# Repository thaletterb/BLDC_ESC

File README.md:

## MSP430 Brushless DC Motor Electronic Speed Controller 

Development of an MSP430 based electronic speed controller. 
* Controls a BLDC electric motor for speed/torque
* Trapezoidal control scheme (6 Step Commutation)

## Background 

* Electronic Speed Control (ESC) is an electronic circuit that controls and regulates the speed of an electric motor. 
* SIMONK ESCs are commonly used for applications such as quadcopters or RC cars
* The purpose of this project is to develop an MSP430 based ESC which replicates the functionality of an off the shelf controller

## Hardware Architecture 

* Current implementation:
  * HW Revision 2
  * 

* Revision History
  * Revision 2 
    * 1 MSP430F5529 PCBA 
    * 1 LHI 2212 920KV Brushless Motor
    * 6 IRLR120N MOSFET N Channel 
    * 3 IR2104S IC Gate Driver 
  * Revision 1 
    * 1 MSP430F5529 Launchpad
    * 1 LHI 2212 920KV Brushless Motor
    * 1 SIMONK 30A ESC
    * 1 Potentiometer to act as throttle input

## Software Architecture

* TI-RTOS
* Current phase of implementation consists of:
  * Using MSP430 to generate varying width PWM signals to the SIMONK ESC
  * Potentiometer attached to analog input P6.1
* Periodics
  * 50Hz CLK

## Software Requirements

Software is based on MSP430F5529 launchpad, running TI-RTOS.

* Code Composer Studio (ver 8.3.1)
  * http://www.ti.com/tool/CCSTUDIO
* TI-RTOS MSP43x 2.20.00.06 
  * http://software-dl.ti.com/dsps/dsps_public_sw/sdo_sb/targetcontent/tirtos/index.html

## References
* https://en.wikipedia.org/wiki/Electronic_speed_control 
* https://www.instructables.com/id/Make-Your-Own-ESC/ 
* http://www.ti.com/lit/ug/spruhu4e/spruhu4e.pdf
* https://simple-circuit.com/arduino-sensorless-bldc-motor-controller-esc/

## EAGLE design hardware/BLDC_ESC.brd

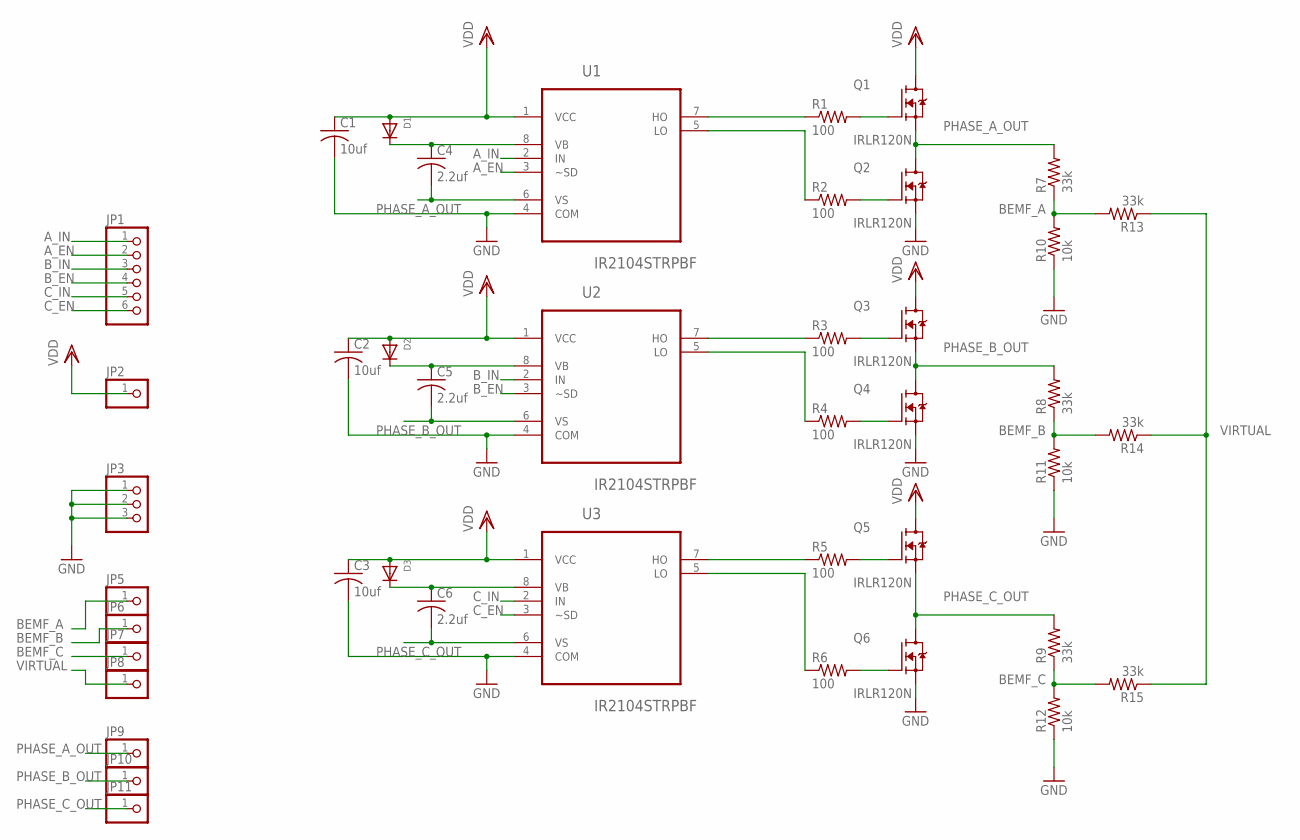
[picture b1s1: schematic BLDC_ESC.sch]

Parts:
C1, C2, C3: 10uf; C0805K
C4, C5, C6: 2.2uf; C0805K
D1, D2, D3: DIODESOD-123; SOD-123
JP1: PINHD-1X6; 1X06
JP2, JP5, JP6, JP7, JP8, JP9, JP10, JP11: PINHD-1X1; 1X01
JP3: PINHD-1X3; 1X03
Q1, Q2, Q3, Q4, Q5, Q6: IRLR120N; DPAK229P990X239-3N
R1, R2, R3, R4, R5, R6: 100; R0805
R7, R8, R9, R13, R14, R15: 33k; R0805
R10, R11, R12: 10k; R0805
U1, U2, U3: IR2104STRPBF; SOIC127P600X175-8N

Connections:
A_EN: JP1.2, U1.3 (~SD)
A_IN: JP1.1, U1.2 (IN)
BEMF_A: JP5.1, R7.1, R10.2, R13.2
BEMF_B: JP6.1, R8.1, R11.2, R14.2
BEMF_C: JP7.1, R9.1, R12.2, R15.2
B_EN: JP1.4, U2.3 (~SD)
B_IN: JP1.3, U2.2 (IN)
C_EN: JP1.6, U3.3 (~SD)
C_IN: JP1.5, U3.2 (IN)
GND: C1.2, C2.2, C3.2, JP3.1, JP3.2, JP3.3, Q2.2 (S), Q4.2 (S), Q6.2 (S), R10.1, R11.1, R12.1, U1.4 (COM), U2.4 (COM), U3.4 (COM)
unnamed: Q1.1 (G), R1.2
unnamed: R1.1, U1.7 (HO)
unnamed: R2.1, U1.5 (LO)
unnamed: Q2.1 (G), R2.2
unnamed: C6.1, D3.C, U3.8 (VB)
unnamed: C5.1, D2.C, U2.8 (VB)
unnamed: C4.1, D1.C, U1.8 (VB)
unnamed: R3.1, U2.7 (HO)
unnamed: Q3.1 (G), R3.2
unnamed: R4.1, U2.5 (LO)
unnamed: Q4.1 (G), R4.2
unnamed: R5.1, U3.7 (HO)
unnamed: Q5.1 (G), R5.2
unnamed: R6.1, U3.5 (LO)
unnamed: Q6.1 (G), R6.2
PHASE_A_OUT: C4.2, JP9.1, Q1.2 (S), Q2.3 (D), R7.2, U1.6 (VS)
PHASE_B_OUT: C5.2, JP10.1, Q3.2 (S), Q4.3 (D), R8.2, U2.6 (VS)
PHASE_C_OUT: C6.2, JP11.1, Q5.2 (S), Q6.3 (D), R9.2, U3.6 (VS)
VDD: C1.1, C2.1, C3.1, D1.A, D2.A, D3.A, JP2.1, Q1.3 (D), Q3.3 (D), Q5.3 (D), U1.1 (VCC), U2.1 (VCC), U3.1 (VCC)
VIRTUAL: JP8.1, R13.1, R14.1, R15.1

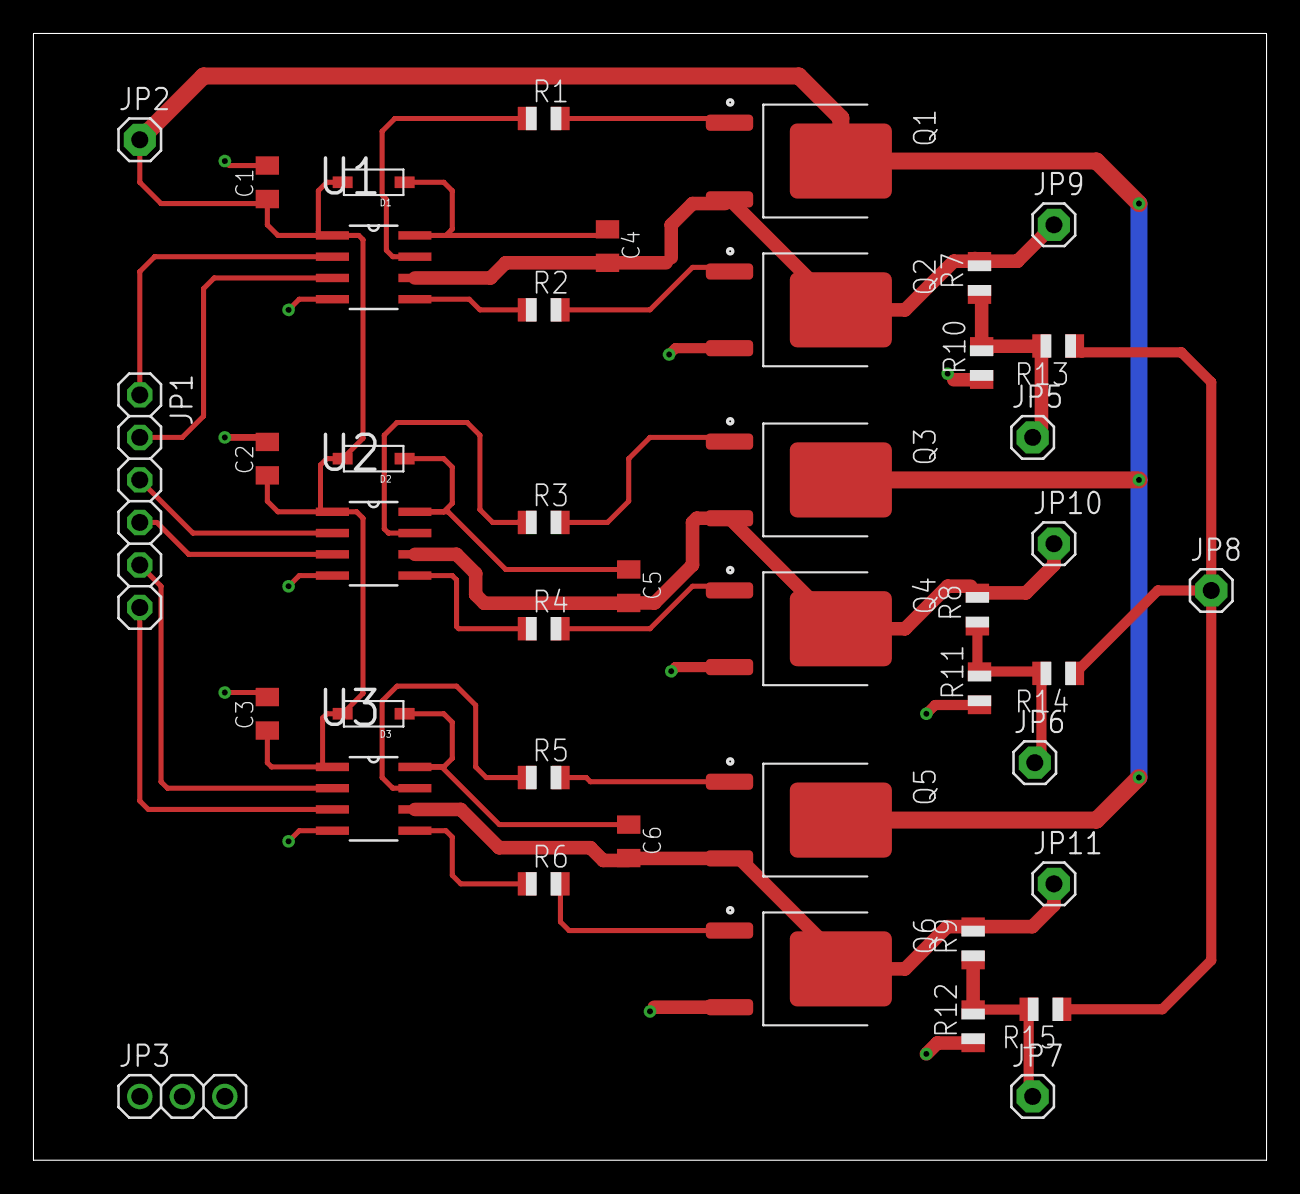
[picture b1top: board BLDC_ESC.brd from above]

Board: 2 copper layers, 73.7 x 67.3 mm, 43 parts (0 on the bottom side), 30 nets.

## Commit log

2018-05-26 Use GPIO as basic PWM pulse * Enable GPIO1_6 as output * Use semaphore to send task * Started using PWM - WIP
2018-06-03 Create PWM module
2018-07-25 Implement Motor Control Module * Create header and module file * Implement first pass of state machine * Use module within main * Demo code: Toggle through different states/modes
2018-07-26 Create top level ESC module * Create new module * Update 50hz CLK callback function * Use new module in main
2018-07-27 Reorganize directory structure
2018-07-29 First readme commit
2018-07-30 Create ADC driver * Default initialization to P6.1 * Demo blink LED when ADC input is 1/2 resolution
2018-07-31 Create Throttle Module * Create new module and interface * Control PWM based on throttle position
2018-08-17 Break PWM into interface and driver
2018-08-17 Use new PWM interface instead
2018-08-17 Split up more interface and driver code
2018-08-17 REVISIT: Use PwmDriver API in MotorControl
2018-08-17 SQUASH: Move includes
2018-11-23 Implement Basic 6 step commutation * Configure new GPIOs and PWM * Uses hardcoded 8us on and 42us off for PWM chopping
2020-07-17 Create 1Hz Clock Periodic
2020-07-18 Working commit - TODO: Cleanup

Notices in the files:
parts and their libraries:
CinchConnectivitySolution: COPYRIGHT: Copyright (C) 2018 Accelerated Designs. All rights reserved
